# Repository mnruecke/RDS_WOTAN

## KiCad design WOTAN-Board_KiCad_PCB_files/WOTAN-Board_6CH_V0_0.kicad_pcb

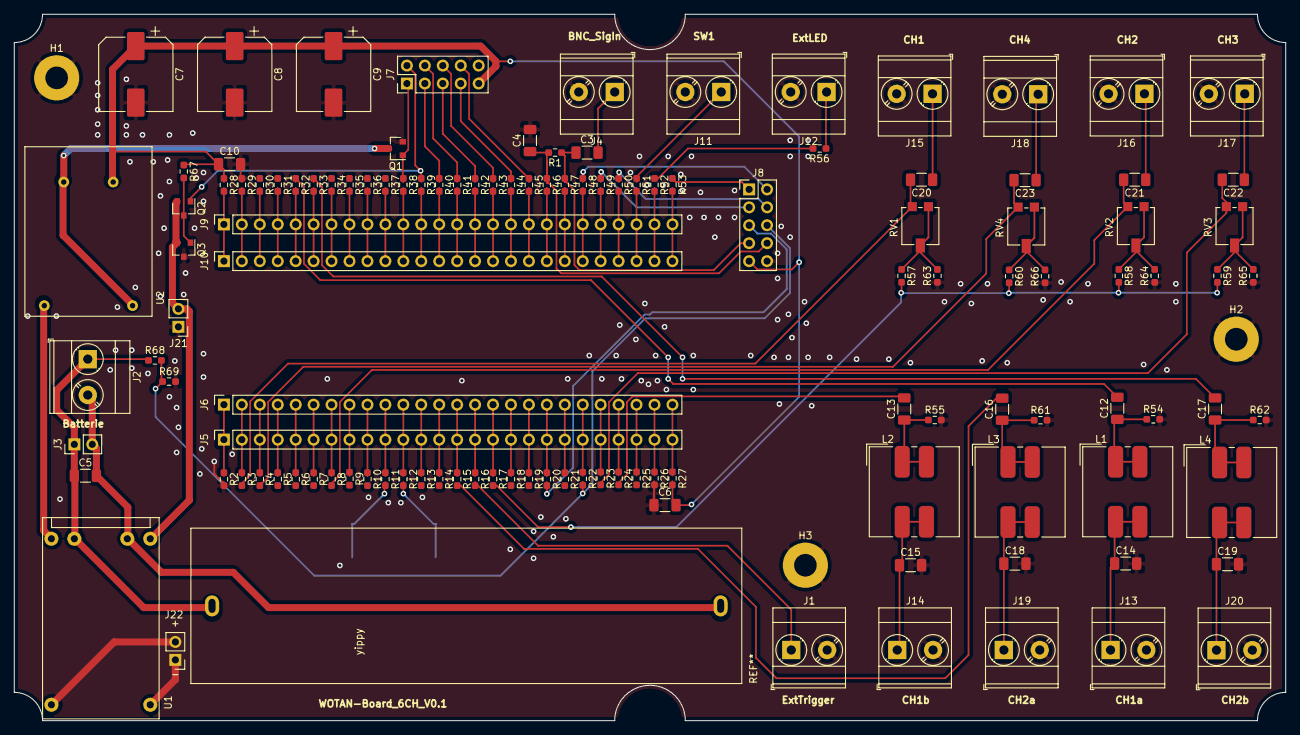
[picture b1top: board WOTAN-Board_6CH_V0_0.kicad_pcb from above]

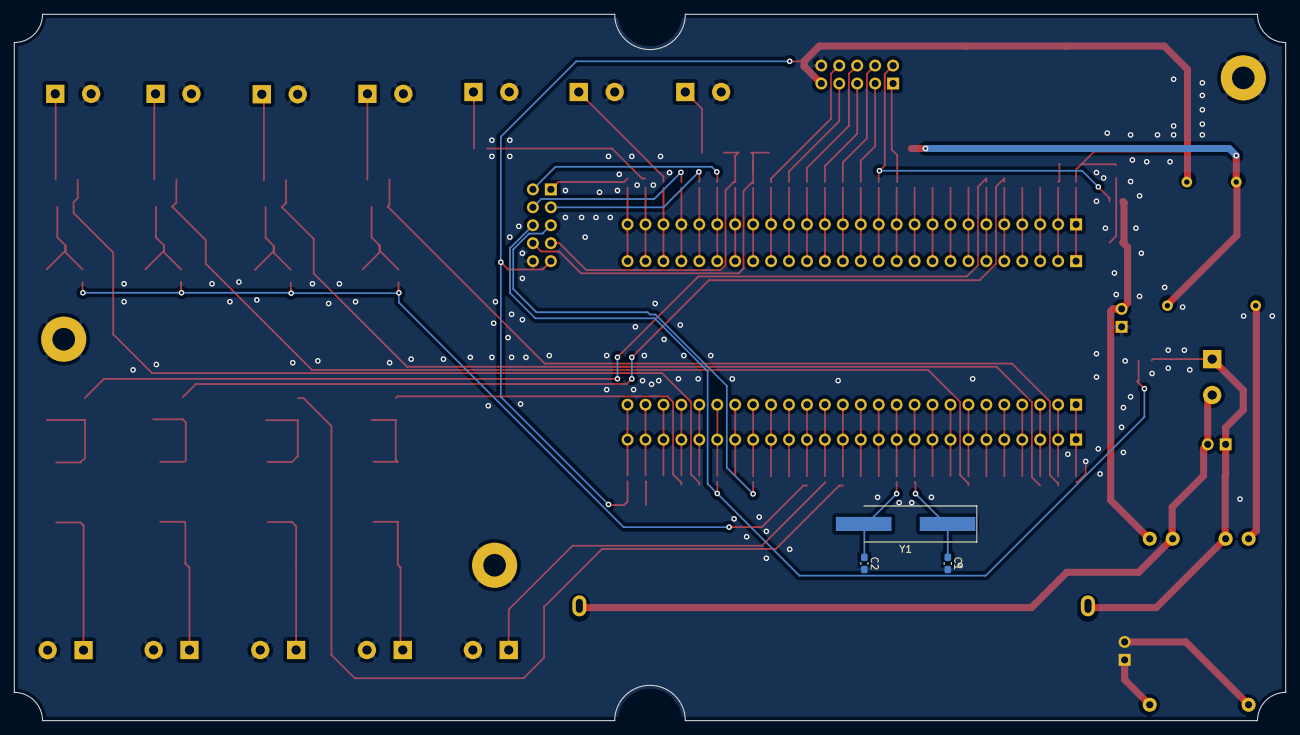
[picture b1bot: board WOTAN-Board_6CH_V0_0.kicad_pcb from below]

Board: 2 copper layers, 180.0 x 100.0 mm, 130 parts (3 on the bottom side), 108 nets.

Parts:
C1: 33p; C_0603_1608Metric_Pad1.08x0.95mm_HandSolder
C2: 33p (18p eingelötet); C_0603_1608Metric_Pad1.08x0.95mm_HandSolder
C3, C4, C5, C6, C10, C14, C15, C18, C19, C20, C21, C22, C23: 100n; C_1206_3216Metric_Pad1.33x1.80mm_HandSolder
C7, C8, C9: 1500u; CP_Elec_10x10
C12, C13, C16, C17: 100n?; C_1206_3216Metric_Pad1.33x1.80mm_HandSolder
H1, H2, H3: MountingHole_Pad; MountingHole_3.2mm_M3_Pad
J1, J2, J4, J11, J12, J13, J14, J15, J16, J17, J18, J19, J20: Conn_01x02_Female; TerminalBlock_Phoenix_MKDS-3-2-5.08_1x02_P5.08mm_Horizontal
J3, J21, J22: Conn_01x02_Male; PinHeader_1x02_P2.54mm_Vertical
J5, J6, J9, J10: Conn_01x26_Female; PinSocket_1x26_P2.54mm_Vertical
J7, J8: Conn_02x05_Odd_Even; PinHeader_2x05_P2.54mm_Vertical
L1, L2, L3, L4: 1mH; L_Bourns_SRF1260
Q1, Q2, Q3: Q_NMOS_GSD; SOT-23
R1, R68, R69: 1M; R_0603_1608Metric_Pad0.98x0.95mm_HandSolder
R2, R3, R4, R5, R6, R7, R8, R9, R10, R11, R12, R13, R14, R15, R16, R17, R18, R19, R20, R21, R22, R23, R24, R25, R26, R27, R28, R29, R30, R31, R32, R33, R34, R35, R36, R37, R38, R39, R40, R41, R42, R43, R44, R45, R46, R47, R48, R49, R50, R51, R52, R53, R57, R58, R59, R60, R63, R64, R65, R66: 0; R_0603_1608Metric_Pad0.98x0.95mm_HandSolder
R54, R55, R61, R62: 2k; R_0603_1608Metric_Pad0.98x0.95mm_HandSolder
R56: 270; R_0603_1608Metric_Pad0.98x0.95mm_HandSolder
R67: 10M; R_0603_1608Metric_Pad0.98x0.95mm_HandSolder
RV1, RV2, RV3, RV4: 5k; Potentiometer_Vishay_TS53YL_Vertical
U1: LiPo_Charger
U2: UpStep_3Vto5V; UpStep3Vto5V
Y1: 18MHz; Crystal_SMD_HC49-SD_HandSoldering

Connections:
+BATT: C5.1, J2.1, J3.1, R68.1, U1.2
/-BATT: C5.2, J2.2, J3.2, U1.3
/CH1: C20.2, R3.2, RV1.1
/CH1a: C12.2, R32.1
/CH1b: C13.2, R24.2
/CH2: C21.2, R8.2, RV2.1
/CH2a: C16.2, R15.2
/CH2b: C17.2, R33.1
/CH3: C22.2, R23.2, RV3.1
/CH4: C23.2, R4.2, RV4.1
/COM_IDAC: R17.2, R57.2, R58.2, R59.2, R60.2
/ChargeOut+: U1.1, U2.1
/ChargeOut-: J21.2, Q2.2, Q3.2, U1.4
/DCDC_CTRL: J7.1, Q1.1, R38.1
/DCDC_ONOFF: Q1.3, U2.2, U2.3
/ExtTrigger: J1.1, R16.2
/LED1: R52.1, R56.2
/MainSig_inN: C4.1, J8.8, R1.2, R46.1
/MainSig_inP: C3.1, J8.7, R1.1, R47.1
/P12_2: J7.3, R40.1
/P12_3: J7.4, R41.1
/P12_4: J7.5, R42.1
/P12_5: J7.6, R43.1
/P12_6: J7.7, R44.1
/P12_7: J7.8, R45.1
/PWR_EN: J7.2, Q2.1, R39.1
/SW1: J11.1, R51.1
/VDD: C6.2, C7.1, C8.1, C9.1, C10.1, J7.9, J8.9, R27.2, R28.1, R67.1, U2.4
/XTAL1: C1.1, R11.2, Y1.1
/XTAL2: C2.1, R12.2, Y1.2
/aux_sig1: J8.1, R53.1
/aux_sig2: J8.2, R48.1
/aux_sig3: J8.3, R49.1
/aux_sig4: J8.4, R50.1
/aux_sig5: J8.5, R20.2
/aux_sig6: J8.6, R22.2, R68.2, R69.1
GND: C1.2, C2.2, C4.2, C6.1, C7.2, C8.2, C9.2, C10.2, C14.2, C15.2, C18.2, C19.2, H1.1, H2.1, H3.1, J1.2, J4.2, J7.10, J8.10, J11.2, J12.2, J13.2, J14.2, J15.2, J16.2, J17.2, J18.2, J19.2, J20.2, J21.1, Q1.2, Q3.3, R2.2, R26.2, R29.1, R54.2, R55.2, R61.2, R62.2, R63.1, R64.1, R65.1, R66.1, R69.2
unnamed: C3.2, J4.1
unnamed: C12.1, L1.1, L1.2, R54.1
unnamed: C13.1, L2.1, L2.2, R55.1
unnamed: C14.1, J13.1, L1.3, L1.4
unnamed: C15.1, J14.1, L2.3, L2.4
unnamed: C16.1, L3.1, L3.2, R61.1
unnamed: C17.1, L4.1, L4.2, R62.1
unnamed: C18.1, J19.1, L3.3, L3.4
unnamed: C19.1, J20.1, L4.3, L4.4
unnamed: C20.1, J15.1
unnamed: C21.1, J16.1
unnamed: C22.1, J17.1
unnamed: C23.1, J18.1
unnamed: J5.1, J6.1, R2.1
unnamed: J5.2, J6.2, R3.1
unnamed: J5.3, J6.3, R4.1
unnamed: J5.4, J6.4, R5.1
unnamed: J5.5, J6.5, R6.1
unnamed: J5.6, J6.6, R7.1
unnamed: J5.7, J6.7, R8.1
unnamed: J5.8, J6.8, R9.1
unnamed: J5.9, J6.9, R10.1
unnamed: J5.10, J6.10, R11.1
unnamed: J5.11, J6.11, R12.1
unnamed: J5.12, J6.12, R13.1
unnamed: J5.13, J6.13, R14.1
unnamed: J5.14, J6.14, R15.1
unnamed: J5.15, J6.15, R16.1
unnamed: J5.16, J6.16, R17.1
unnamed: J5.17, J6.17, R18.1
unnamed: J5.18, J6.18, R19.1
unnamed: J5.19, J6.19, R20.1
unnamed: J5.20, J6.20, R21.1
unnamed: J5.21, J6.21, R22.1
unnamed: J5.22, J6.22, R23.1
unnamed: J5.23, J6.23, R24.1
unnamed: J5.24, J6.24, R25.1
unnamed: J5.25, J6.25, R26.1
unnamed: J5.26, J6.26, R27.1
unnamed: J9.1, J10.1, R28.2
unnamed: J9.2, J10.2, R29.2
unnamed: J9.3, J10.3, R30.2
unnamed: J9.4, J10.4, R31.2
unnamed: J9.5, J10.5, R32.2
unnamed: J9.6, J10.6, R33.2
unnamed: J9.7, J10.7, R34.2
unnamed: J9.8, J10.8, R35.2
unnamed: J9.9, J10.9, R36.2
unnamed: J9.10, J10.10, R37.2
unnamed: J9.11, J10.11, R38.2
unnamed: J9.12, J10.12, R39.2
unnamed: J9.13, J10.13, R40.2
unnamed: J9.14, J10.14, R41.2
unnamed: J9.15, J10.15, R42.2
unnamed: J9.16, J10.16, R43.2
unnamed: J9.17, J10.17, R44.2
unnamed: J9.18, J10.18, R45.2
unnamed: J9.19, J10.19, R46.2
unnamed: J9.20, J10.20, R47.2
unnamed: J9.21, J10.21, R48.2
unnamed: J9.22, J10.22, R49.2
unnamed: J9.23, J10.23, R50.2
unnamed: J9.24, J10.24, R51.2
unnamed: J9.25, J10.25, R52.2
unnamed: J9.26, J10.26, R53.2
unnamed: J12.1, R56.1
unnamed: Q2.3, Q3.1, R67.2
unnamed: R57.1, R63.2, RV1.2, RV1.3
unnamed: R58.1, R64.2, RV2.2, RV2.3
unnamed: R59.1, R65.2, RV3.2, RV3.3
unnamed: R60.1, R66.2, RV4.2, RV4.3

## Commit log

2023-01-04 raw files of spectrometer console and pcb files
2023-02-03 rawfiles for RDS spectrometer
2023-02-03 make repo clean
2023-02-21 adjust .gitignore and simplify run_sequence_6channel.py
2023-02-21 add data evaluation *.py script
2023-02-22 simplify WOTAN 6CH to 4 channel version
2023-02-22 add programmable rx-gain
2023-02-22 modify prog. rx gain to higher bandwidth configuration
2023-02-22 remove ascii debug routines from main.c
2023-02-22 add averaging into *.py file
2023-02-23 small code clean ups
2023-02-24 introduce board coupling code (stubs only)
2023-02-24 Expand test code for direct board coupling
2023-02-25 fixing sync test routine (initiation command still not implemented)
2023-02-26 add slave module in project folder (master-slave bridge still not implemented)
2023-02-27 master-slave uart communication running, but command gets transmitted errornes
2023-03-01 Master Slave combination working if two usbfs connections are used for adc data
2023-03-01 Master Slave with two usbfs working - but with drastic noise increase
2023-03-04 Make separate branch for multi_board version
2023-03-04 move master slave multiboard code into separate branch
2023-03-05 clean up *.py files
2023-03-05 add generate_wavelets() to rds_essentials.py as new sequence gen. method
2023-04-06 running - but needs reset after sequence_write for rx to work
2023-04-07 add wotan rds v2 (i.e., wotan from scratch)
2023-04-08 wotan rds v2: 4 programmable dac channels running from flash
2023-04-09 added adcs to rds v2 - data corupted if n_adc_samples > 12800 - psoc freezes after sending adc data
2023-04-10 fixing adc sampling -> 30 000 samples / 15 ms, send adc data in 60 byte packages each requested individually
2023-04-12 fix clock tree behaviour diff between reset and power cycling, minor clean ups
2023-04-14 complete wavelet generation, trigger out indicates adc sampling window (+ safety margin)
2023-04-14 add spectroscopy sequence to rds_v2_lib
